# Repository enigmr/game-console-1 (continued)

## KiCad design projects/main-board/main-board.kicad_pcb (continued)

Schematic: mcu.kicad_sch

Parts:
C1, C5, C6, C7, C8, C10, C12, C13, C14, C15, C18, C21, C23, C25, C26, C28, C29, C31, C33, C34, C40, C41, C42, C44, C45, C47: 100nF 10V; C_0402_1005Metric
C2, C9, C17, C20, C22, C30, C32, C36, C37, C38, C39, C43, C46, C48: 1uF 10V; C_0402_1005Metric
C3: 2.2nF 10V; C_0402_1005Metric
C4: 4.7uF 10V; C_0402_1005Metric
C11, C19, C27, C35: 22uF 10V; C_0603_1608Metric
C16, C24: 10uF 10V; C_0603_1608Metric
C109, C110: 9pF 50V; C_0402_1005Metric
C115, C116: 8pF 50V; C_0402_1005Metric
J1, J2: TC2030; Tag-Connect_TC2030-IDC-NL_2x03_P1.27mm_Vertical
L1: 1uH 2.7A 0.054R; IND_0806
L2: 18R; L_0603_1608Metric
L3: 2.2nH 1.4A 0.018R; L_0603_1608Metric
NT1, NT3, NT4, NT5, NT7, NT8, NT9, NT10, NT11, NT12, NT13, NT14: NetTie_2
R1: 2R; R_0402_1005Metric
R2: 200R; R_0402_1005Metric
R3: 10K; R_0402_1005Metric
R4: 50.1K; R_0402_1005Metric
R5, R6, R7, R8: 2.2K; R_0402_1005Metric
R9, R10, R11, R12, R13, R14, R15, R16, R17, R18, R19, R20, R21, R22, R23, R24, R25, R26, R27, R28, R29, R30, R31, R32, R33, R34, R35, R36, R37, R38, R39, R61, R62, R64, R65: 0R; R_0402_1005Metric
U1: STM32N657X0HxQ; STM32N645A0HxQ
Y2: ABM11W-48.0000MHZ-8-K1Z-T3; ABM11W300000MHZ4B1UT3; Manufacturer_Part_Number ABM11W-48.0000MHZ-8-K1Z-T3; Mouser Part Number 815-11W48-8K1ZT
Y3: ABS06-32.768KHZ-9-1-T; ABS06

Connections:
1V8: C1.1, C10.1, C18.1, C26.1, C34.1, C40.1, L2.1, L3.1, NT1.2, NT3.2, NT4.2, NT7.2, NT8.2, NT10.2, NT11.2, NT13.2, NT14.2, U1.G13 (VDD), U1.H12 (VDD), U1.H13 (VDD), U1.J12 (VDD), U1.J13 (VDD), U1.K13 (VDD); also elsewhere on the board
3V3: J1.1, NT5.2, NT9.2, NT12.2, R5.1, R6.1, R7.1, R8.1; also elsewhere on the board
/Audio/I2C.SCL: R5.2, U1.C11 (PE5); also elsewhere on the board
/Audio/I2C.SDA: R7.2, U1.D11 (PE6); also elsewhere on the board
/Audio/I2S.BCK: U1.E17 (PB6); also elsewhere on the board
/Audio/I2S.DACDAT: U1.E16 (PB7); also elsewhere on the board
/Audio/I2S.LRCK: U1.E15 (PB0); also elsewhere on the board
/Audio/I2S.MCLK: U1.F15 (PE2); also elsewhere on the board
/Controllers/BUTTONS.B0: U1.R3 (PF0); also elsewhere on the board
/Controllers/BUTTONS.B1: U1.T1 (PF12); also elsewhere on the board
/Controllers/BUTTONS.B2: U1.P2 (PG4); also elsewhere on the board
/Controllers/BUTTONS.B3: U1.F4 (PH4); also elsewhere on the board
/Controllers/BUTTONS.B4: U1.L2 (PF4); also elsewhere on the board
/Controllers/BUTTONS.B5: U1.B1 (PH3); also elsewhere on the board
/Controllers/BUTTONS.B6: U1.L1 (PG7); also elsewhere on the board
/Controllers/BUTTONS.B7: U1.M1 (PF7); also elsewhere on the board
/Controllers/BUTTONS.B8: U1.B2 (PH6); also elsewhere on the board
/Controllers/BUTTONS.B9: U1.P1 (PF9); also elsewhere on the board
/ESP32/ESP32_GPIO.2: U1.C8 (PC12); also elsewhere on the board
/ESP32/ESP32_GPIO.3: U1.A13 (PD10); also elsewhere on the board
/ESP32/ESP32_GPIO.8: U1.F3 (PC13); also elsewhere on the board
/ESP32/ESP32_GPIO.9: U1.A14 (PD1); also elsewhere on the board
/ESP32/ESP32_UART.RX: U1.F17 (PE1); also elsewhere on the board
/ESP32/ESP32_UART.TX: U1.F16 (PE0); also elsewhere on the board
/Flash/FLASH_OCTOSPI.CS_N: R10.2; also elsewhere on the board
/Flash/FLASH_OCTOSPI.DQS: R9.2; also elsewhere on the board
/Flash/FLASH_OCTOSPI.RESET_N: U1.T16 (PN7); also elsewhere on the board
/Flash/FLASH_OCTOSPI.SCLK: R15.2; also elsewhere on the board
/Flash/FLASH_OCTOSPI.SIO0: R11.2; also elsewhere on the board
/Flash/FLASH_OCTOSPI.SIO1: R12.2; also elsewhere on the board
/Flash/FLASH_OCTOSPI.SIO2: R13.2; also elsewhere on the board
/Flash/FLASH_OCTOSPI.SIO3: R14.2; also elsewhere on the board
/Flash/FLASH_OCTOSPI.SIO4: R16.2; also elsewhere on the board
/Flash/FLASH_OCTOSPI.SIO5: R17.2; also elsewhere on the board
/Flash/FLASH_OCTOSPI.SIO6: R18.2; also elsewhere on the board
/Flash/FLASH_OCTOSPI.SIO7: R19.2; also elsewhere on the board
/Haptics/LEFT_MOTOR_EN: U1.D5 (PQ5); also elsewhere on the board
/Haptics/MOTOR_PWR_EN: U1.A16 (PE9); also elsewhere on the board
/Haptics/RIGHT_MOTOR_EN: U1.G5 (PQ7); also elsewhere on the board
/LCD/BACKLIGHT_PWM: U1.B9 (PC6); also elsewhere on the board
/LCD/LCD.B0: U1.R6 (PG15); also elsewhere on the board
/LCD/LCD.B1: U1.R12 (PA7); also elsewhere on the board
/LCD/LCD.B2: U1.U7 (PA12); also elsewhere on the board
/LCD/LCD.B3: U1.T7 (PA11); also elsewhere on the board
/LCD/LCD.B4: U1.R7 (PA10); also elsewhere on the board
/LCD/LCD.B5: U1.P7 (PA9); also elsewhere on the board
/LCD/LCD.B6: U1.U8 (PA8); also elsewhere on the board
/LCD/LCD.B7: U1.T8 (PA2); also elsewhere on the board
/LCD/LCD.CLK: U1.R8 (PA5); also elsewhere on the board
/LCD/LCD.DE: U1.U9 (PG13); also elsewhere on the board
/LCD/LCD.EN: U1.U14 (PA4); also elsewhere on the board
/LCD/LCD.G0: U1.T9 (PG12); also elsewhere on the board
/LCD/LCD.G1: U1.R9 (PG1); also elsewhere on the board
/LCD/LCD.G2: U1.P9 (PA1); also elsewhere on the board
/LCD/LCD.G3: U1.U10 (PA0); also elsewhere on the board
/LCD/LCD.G4: U1.T10 (PG10); also elsewhere on the board
/LCD/LCD.G5: U1.R10 (PB12); also elsewhere on the board
/LCD/LCD.G6: U1.P10 (PB11); also elsewhere on the board
/LCD/LCD.G7: U1.T14 (PG8); also elsewhere on the board
/LCD/LCD.HSYNC: U1.P8 (PA6); also elsewhere on the board
/LCD/LCD.R0: U1.R13 (PG0); also elsewhere on the board
/LCD/LCD.R1: U1.L4 (PF10); also elsewhere on the board
/LCD/LCD.R2: U1.U12 (PB5(JTDO/TRACESWO)); also elsewhere on the board
/LCD/LCD.R3: U1.T12 (PB4(NJTRST)); also elsewhere on the board
/LCD/LCD.R4: U1.M2 (PF3); also elsewhere on the board
/LCD/LCD.R5: U1.P12 (PA15(JTDI)); also elsewhere on the board
/LCD/LCD.R6: U1.U13 (PG11); also elsewhere on the board
/LCD/LCD.R7: U1.T13 (PG9); also elsewhere on the board
/LCD/LCD.VSYNC: U1.E11; also elsewhere on the board
/MCU/BOOT0: U1.G4 (BOOT0)
/MCU/DEBUG_UART.RX: J2.1, U1.C14 (PD14)
/MCU/DEBUG_UART.TX: J2.3, U1.D15 (PB9)
/MCU/ESP32_EN: U1.B17 (PB14); also elsewhere on the board
/MCU/I2C4.SCL: R6.2, U1.A11 (PE13); also elsewhere on the board
/MCU/I2C4.SDA: R8.2, U1.B11 (PE14); also elsewhere on the board
/MCU/NRST: J1.3, U1.G3 (NRST)
/MCU/PMIC_ALERT: U1.R2 (PF13); also elsewhere on the board
/MCU/PMIC_CHARGE_EN: U1.R1 (PG3); also elsewhere on the board
/MCU/PMIC_INPUT_VALID: U1.N1 (PF15); also elsewhere on the board
/MCU/PMIC_STATUS: U1.N2 (PF14); also elsewhere on the board
/MCU/RAM_HEXASPI.CLK: R23.2; also elsewhere on the board
/MCU/RAM_HEXASPI.CS_N: R20.2; also elsewhere on the board
/MCU/RAM_HEXASPI.D0: R24.2; also elsewhere on the board
/MCU/RAM_HEXASPI.D1: R25.2; also elsewhere on the board
/MCU/RAM_HEXASPI.D2: R26.2; also elsewhere on the board
/MCU/RAM_HEXASPI.D3: R27.2; also elsewhere on the board
/MCU/RAM_HEXASPI.D4: R28.2; also elsewhere on the board
/MCU/RAM_HEXASPI.D5: R29.2; also elsewhere on the board
/MCU/RAM_HEXASPI.D6: R30.2; also elsewhere on the board
/MCU/RAM_HEXASPI.D7: R31.2; also elsewhere on the board
/MCU/RAM_HEXASPI.D8: R32.2; also elsewhere on the board
/MCU/RAM_HEXASPI.D9: R33.2; also elsewhere on the board
/MCU/RAM_HEXASPI.D10: R34.2; also elsewhere on the board
/MCU/RAM_HEXASPI.D11: R35.2; also elsewhere on the board
/MCU/RAM_HEXASPI.D12: R36.2; also elsewhere on the board
/MCU/RAM_HEXASPI.D13: R37.2; also elsewhere on the board
/MCU/RAM_HEXASPI.D14: R38.2; also elsewhere on the board
/MCU/RAM_HEXASPI.D15: R39.2; also elsewhere on the board
/MCU/RAM_HEXASPI.DQS0: R21.2; also elsewhere on the board
/MCU/RAM_HEXASPI.DQS1: R22.2; also elsewhere on the board
/MCU/SD.CLK: U1.D9 (PC2); also elsewhere on the board
/MCU/SD.CMD: U1.E10 (PC3); also elsewhere on the board
/MCU/SD.D0: U1.A10 (PC4); also elsewhere on the board
/MCU/SD.D1: U1.B10 (PC5); also elsewhere on the board
/MCU/SD.D2: U1.C10 (PC0); also elsewhere on the board
/MCU/SD.D3: U1.D10 (PE4); also elsewhere on the board
/MCU/SD.DETECT: U1.P14 (PN12)
/MCU/SWCLK: J1.4, U1.T6 (PA14(JTCK/SWCLK))
/MCU/SWDIO: J1.2, U1.U6 (PA13(JTMS/SWDIO))
/MCU/USB.DN: U1.A5 (OTG1_HSDM); also elsewhere on the board
/MCU/USB.DP: U1.B5 (OTG1_HSDP); also elsewhere on the board
/MCU/USB_CC1: U1.A6 (UCPD1_CC1)
/MCU/USB_CC2: U1.B6 (UCPD1_CC2)
GND: C1.2, C2.2, C3.2, C4.2, C5.2, C6.2, C7.2, C8.2, C9.2, C10.2, C11.2, C12.2, C13.2, C14.2, C15.2, C16.2, C17.2, C18.2, C19.2, C20.2, C21.2, C22.2, C23.2, C24.2, C25.2, C26.2, C27.2, C28.2, C29.2, C30.2, C31.2, C32.2, C33.2, C34.2, C35.2, C36.2, C37.2, C38.2, C39.2, C40.2, C41.2, C42.2, C43.2, C44.2, C45.2, C46.2, C47.2, C48.2, C109.2, C110.2, C115.2, C116.2, J1.5, J2.5, R2.2, R4.2, U1.A17 (VSS), U1.F2 (VSSAPMU), U1.F7 (VSS), U1.F10 (VSS), U1.F11 (VSS), U1.F12 (VSS), U1.G6 (VSSAON), U1.G12 (VSS), U1.H1 (VSSSMPS), U1.H2 (VSSSMPS), U1.H3 (VSSSMPS), U1.H4 (VSSSMPS), U1.H5 (VSSSMPS), U1.H6 (VSSSMPS), U1.K12 (VSS), U1.M6 (VSSA), U1.M8 (VSS), U1.M10 (VSS), U1.M12 (VSS), U1.M13 (VSS), U1.N5 (VSS), U1.N7 (VSS), U1.N9 (VSS), U1.N11 (VSS), U1.T2 (VREF-), U1.U1 (VSS), U1.U17 (VSS), Y2.2 (GND), Y2.4 (GND); also elsewhere on the board
unnamed: C3.1, R1.2
unnamed: C109.1, R65.1, Y3.1
unnamed: C110.1, R64.1, Y3.2
unnamed: C115.1, R61.2, Y2.1
unnamed: C116.1, R62.2, Y2.3
unnamed: L1.1, R1.1, U1.J1 (VLXSMPS), U1.J2 (VLXSMPS), U1.J3 (VLXSMPS), U1.J4 (VLXSMPS), U1.J5 (VLXSMPS), U1.J6 (VLXSMPS)
unnamed: R65.2, U1.D1 (PC14-OSC32_IN(OSC32_IN))
unnamed: R64.2, U1.C1 (PC15-OSC32_OUT(OSC32_OUT))
unnamed: R61.1, U1.A7 (PH0-OSC_IN(PH0))
unnamed: R62.1, U1.B7 (PH1-OSC_OUT(PH1))
unnamed: R9.1, U1.P17 (PN0)
unnamed: R10.1, U1.R17 (PN1)
unnamed: R11.1, U1.T17 (PN2)
unnamed: R12.1, U1.R15 (PN3)
unnamed: R13.1, U1.N17 (PN4)
unnamed: R14.1, U1.R16 (PN5)
unnamed: R15.1, U1.P15 (PN6)
unnamed: R16.1, U1.P16 (PN8)
unnamed: R17.1, U1.T15 (PN9)
unnamed: R18.1, U1.U15 (PN10)
unnamed: R19.1, U1.U16 (PN11)
unnamed: R20.1, U1.M17 (PO0)
unnamed: R21.1, U1.K17 (PO2)
unnamed: R22.1, U1.M16 (PO3)
unnamed: R23.1, U1.N16 (PO4)
unnamed: R2.1, U1.C6 (OTG1_TXRTUNE)
unnamed: C12.1, R3.2, R4.1, U1.E1 (VBAT)
unnamed: R24.1, U1.G17 (PP0)
unnamed: R25.1, U1.H16 (PP1)
unnamed: R26.1, U1.J17 (PP2)
unnamed: R27.1, U1.J16 (PP3)
unnamed: R28.1, U1.H15 (PP4)
unnamed: R29.1, U1.J14 (PP5)
unnamed: R30.1, U1.G16 (PP6)
unnamed: R31.1, U1.G15 (PP7)
unnamed: R32.1, U1.L16 (PP8)
unnamed: R33.1, U1.N14 (PP9)
unnamed: R34.1, U1.N15 (PP10)
unnamed: R35.1, U1.L15 (PP11)
unnamed: R36.1, U1.J15 (PP12)
unnamed: R37.1, U1.K14 (PP13)
unnamed: R38.1, U1.L17 (PP14)
unnamed: R39.1, U1.H17 (PP15)
V08CAP: C4.1, U1.F1 (V08CAP)
VBAT: R3.1; also elsewhere on the board
VDDA18ADC: C29.1, NT11.1, U1.N6 (VDDA18ADC)
VDDA18AON: C5.1, NT1.1, U1.A1 (PDR_ON), U1.F6 (VDDA18AON)
VDDA18CSI: C6.1, NT3.1, U1.R5 (VDDA18CSI)
VDDA18PLL: C42.1, NT14.1, U1.M5 (VDDA18PLL)
VDDA18PMU: C13.1, L2.2, U1.G1 (VDDA18PMU)
VDDA18USB: C21.1, NT8.1, U1.C5 (VDDA18USB)
VDDA33USB: C38.1, NT12.1, U1.A4 (VDD33USB)
VDDCORE: C2.1, C9.1, C11.1, C17.1, C19.1, C22.1, C27.1, C30.1, C35.1, C37.1, C43.1, C46.1, C48.1, L1.2, U1.G2 (VFBSMPS), U1.L6 (VDDCORE), U1.L12 (VDDCORE), U1.M7 (VDDCORE), U1.M9 (VDDCORE), U1.M11 (VDDCORE), U1.N8 (VDDCORE), U1.N10 (VDDCORE), U1.N12 (VDDCORE), U1.P11 (VDDCORE)
VDDCSI: C20.1, NT7.1, U1.R4 (VDDCSI)
VDDIO2: C7.1, C14.1, C23.1, C31.1, NT4.1, U1.L13 (VDDIO2), U1.L14 (VDDIO2), U1.M14 (VDDIO2), U1.M15 (VDDIO2)
VDDIO3: C41.1, C45.1, NT13.1, U1.N13 (VDDIO3), U1.P13 (VDDIO3)
VDDIO4: C8.1, C15.1, NT5.1, U1.E8 (VDDIO4), U1.F8 (VDDIO4)
VDDIO5: C25.1, C33.1, NT9.1, U1.E9 (VDDIO5), U1.F9 (VDDIO5)
VDDSMPS: C16.1, C24.1, C32.1, C39.1, C44.1, C47.1, L3.2, U1.K1 (VDDSMPS), U1.K2 (VDDSMPS), U1.K3 (VDDSMPS), U1.K4 (VDDSMPS), U1.K5 (VDDSMPS), U1.K6 (VDDSMPS)
VREF: C28.1, C36.1, NT10.1, U1.U2 (VREF+)

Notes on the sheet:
USART10_RX
SAI1_MCLK_A
USART3_RX
USART3_TX
USART10_TX
TIM8_CH3
TIM8_CH2
SAI1_SD_A
SAI1_SCK_A
TIM9_CH1
SAI1_FS_A

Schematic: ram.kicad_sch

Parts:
C49, C50: 100nF 10V; C_0402_1005Metric
C51, C52: 4.7uF 10V; C_0402_1005Metric
R40: 10K; R_0402_1005Metric
U2: APS256XXN-OBR-BG

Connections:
1V8: C49.1, C50.1, C51.1, C52.1, R40.1, U2.D1 (VDD), U2.E4 (VDD); also elsewhere on the board
/MCU/RAM_HEXASPI.CLK: U2.B2 (CLK); also elsewhere on the board
/MCU/RAM_HEXASPI.CS_N: R40.2, U2.A3 (CE#); also elsewhere on the board
/MCU/RAM_HEXASPI.D0: U2.D3 (ADQ0); also elsewhere on the board
/MCU/RAM_HEXASPI.D1: U2.D2 (ADQ1); also elsewhere on the board
/MCU/RAM_HEXASPI.D2: U2.C4 (ADQ2); also elsewhere on the board
/MCU/RAM_HEXASPI.D3: U2.D4 (ADQ3); also elsewhere on the board
/MCU/RAM_HEXASPI.D4: U2.D5 (ADQ4); also elsewhere on the board
/MCU/RAM_HEXASPI.D5: U2.E3 (ADQ5); also elsewhere on the board
/MCU/RAM_HEXASPI.D6: U2.E2 (ADQ6); also elsewhere on the board
/MCU/RAM_HEXASPI.D7: U2.E1 (ADQ7); also elsewhere on the board
/MCU/RAM_HEXASPI.D8: U2.C2 (DQ8); also elsewhere on the board
/MCU/RAM_HEXASPI.D9: U2.B1 (DQ9); also elsewhere on the board
/MCU/RAM_HEXASPI.D10: U2.A2 (DQ10); also elsewhere on the board
/MCU/RAM_HEXASPI.D11: U2.A4 (DQ11); also elsewhere on the board
/MCU/RAM_HEXASPI.D12: U2.A5 (DQ12); also elsewhere on the board
/MCU/RAM_HEXASPI.D13: U2.B4 (DQ13); also elsewhere on the board
/MCU/RAM_HEXASPI.D14: U2.B5 (DQ14); also elsewhere on the board
/MCU/RAM_HEXASPI.D15: U2.C5 (DQ15); also elsewhere on the board
/MCU/RAM_HEXASPI.DQS0: U2.C3 (DQS/DM0); also elsewhere on the board
/MCU/RAM_HEXASPI.DQS1: U2.B3 (DQS/DM1); also elsewhere on the board
GND: C49.2, C50.2, C51.2, C52.2, U2.C1 (VSS), U2.E5 (VSS); also elsewhere on the board

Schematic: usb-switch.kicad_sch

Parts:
C74: 100nF 10V; C_0402_1005Metric
U8: TS3USB221ARSER

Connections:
3V3: C74.1, U8.10 (VCC); also elsewhere on the board
/MCU/USB.DN: U8.2 (1D-); also elsewhere on the board
/MCU/USB.DP: U8.1 (1D+); also elsewhere on the board
/Power/DATAMUX: U8.9 (S); also elsewhere on the board
/Power/USB.DN: U8.4 (2D-); also elsewhere on the board
/Power/USB.DP: U8.3 (2D+); also elsewhere on the board
/USB Switch/USB_UP.DN: U8.7 (D-); also elsewhere on the board
/USB Switch/USB_UP.DP: U8.8 (D+); also elsewhere on the board
GND: C74.2, U8.5 (GND), U8.6 (OE_N); also elsewhere on the board

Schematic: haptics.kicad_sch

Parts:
C100, C102: 10uF 10V; C_0603_1608Metric
C101, C103: 100nF 10V; C_0402_1005Metric
NT2: NetTie_2
Q1, Q2: ZXTN4240F-7; SOT23_ZXTN_DIO
R57: 10K; R_0402_1005Metric
R58, R59: 1K; R_0402_1005Metric
U12: TLV74330PDBVR

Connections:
/Controllers/LEFT_MOTOR.N: Q1.1 (C); also elsewhere on the board
/Controllers/LEFT_MOTOR.P: C102.1, C103.1, NT2.1, U12.5 (OUT); also elsewhere on the board
/Controllers/RIGHT_MOTOR.N: Q2.1 (C); also elsewhere on the board
/Haptics/LEFT_MOTOR_EN: R58.1; also elsewhere on the board
/Haptics/MOTOR_PWR_EN: R57.1, U12.3 (EN); also elsewhere on the board
/Haptics/RIGHT_MOTOR_EN: R59.1; also elsewhere on the board
GND: C100.2, C101.2, C102.2, C103.2, Q1.3 (E), Q2.3 (E), R57.2, U12.2 (GND), U12.4 (NC); also elsewhere on the board
unnamed: Q1.2 (B), R58.2
unnamed: Q2.2 (B), R59.2
VSYS: C100.1, C101.1, U12.1 (IN); also elsewhere on the board

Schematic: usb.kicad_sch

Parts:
J7: USB4105-GF-A

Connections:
/USB Switch/USB_UP.DN: J7.A7 (Dn1), J7.B7 (Dn2); also elsewhere on the board
/USB Switch/USB_UP.DP: J7.A6 (Dp1), J7.B6 (Dp2); also elsewhere on the board
/USB/USB_CC1: J7.A5 (CC1); also elsewhere on the board
/USB/USB_CC2: J7.B5 (CC2); also elsewhere on the board
GND: J7.A1 (GND), J7.B1 (GND), J7.SH1 (GND), J7.SH2 (GND), J7.SH3 (GND), J7.SH4 (GND); also elsewhere on the board
VBUS: J7.A4 (VBUS), J7.B4 (VBUS); also elsewhere on the board

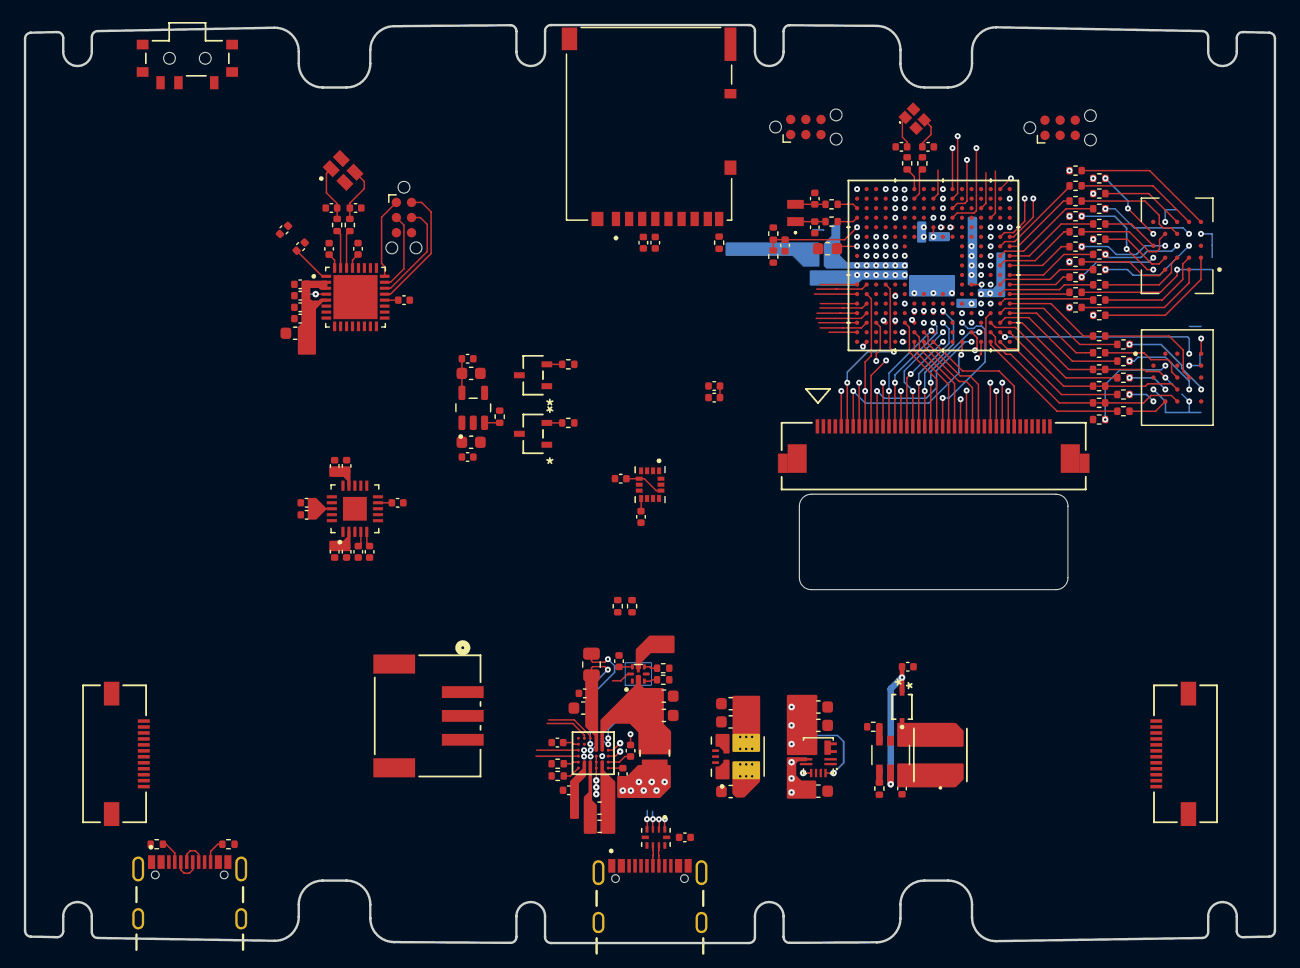
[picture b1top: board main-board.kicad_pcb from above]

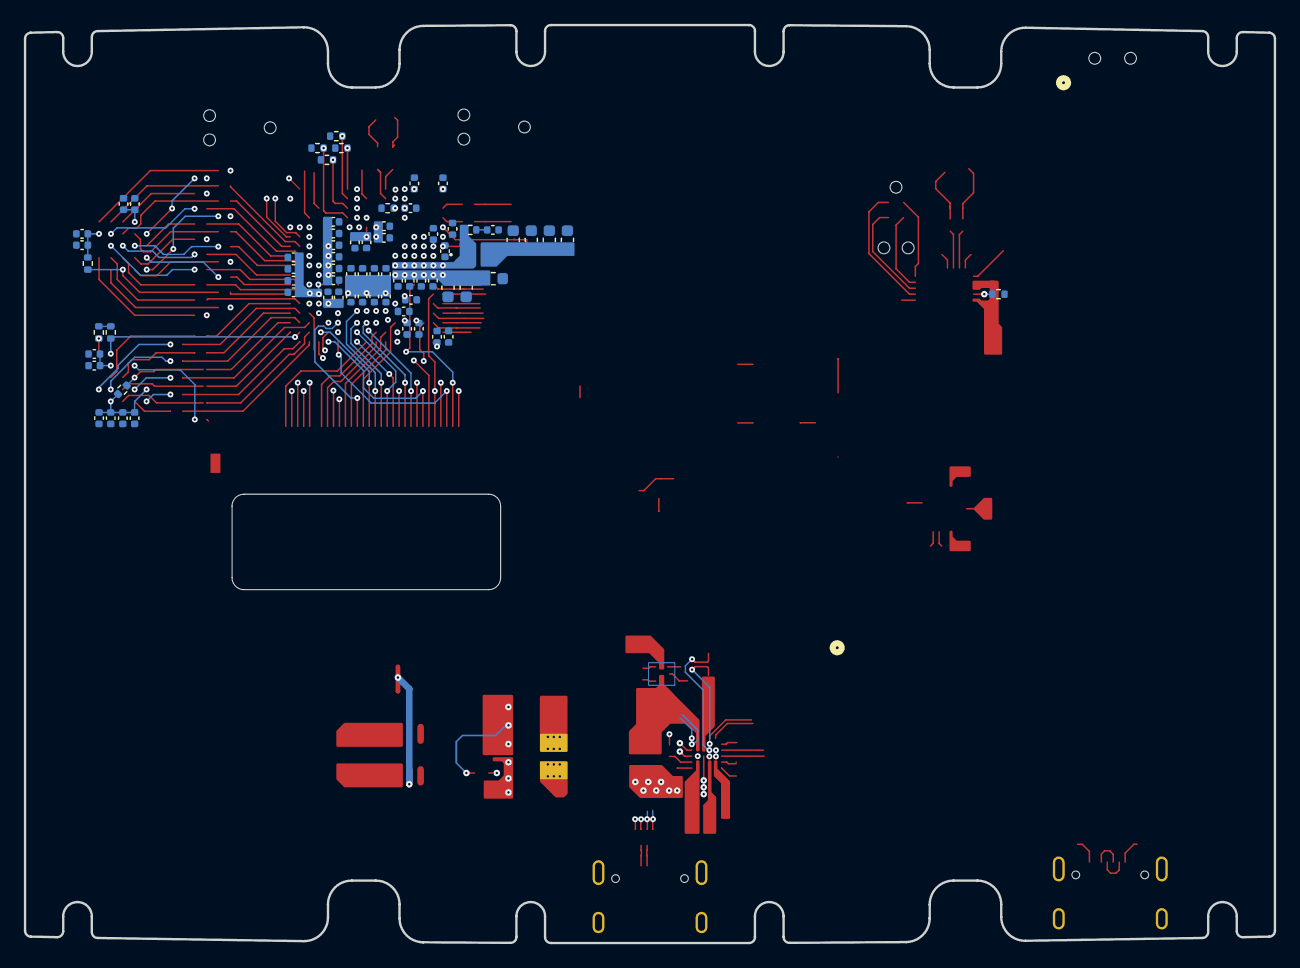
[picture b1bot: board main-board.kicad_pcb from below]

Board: 6 copper layers, 104.8 x 77.0 mm, 213 parts (70 on the bottom side), 219 nets.

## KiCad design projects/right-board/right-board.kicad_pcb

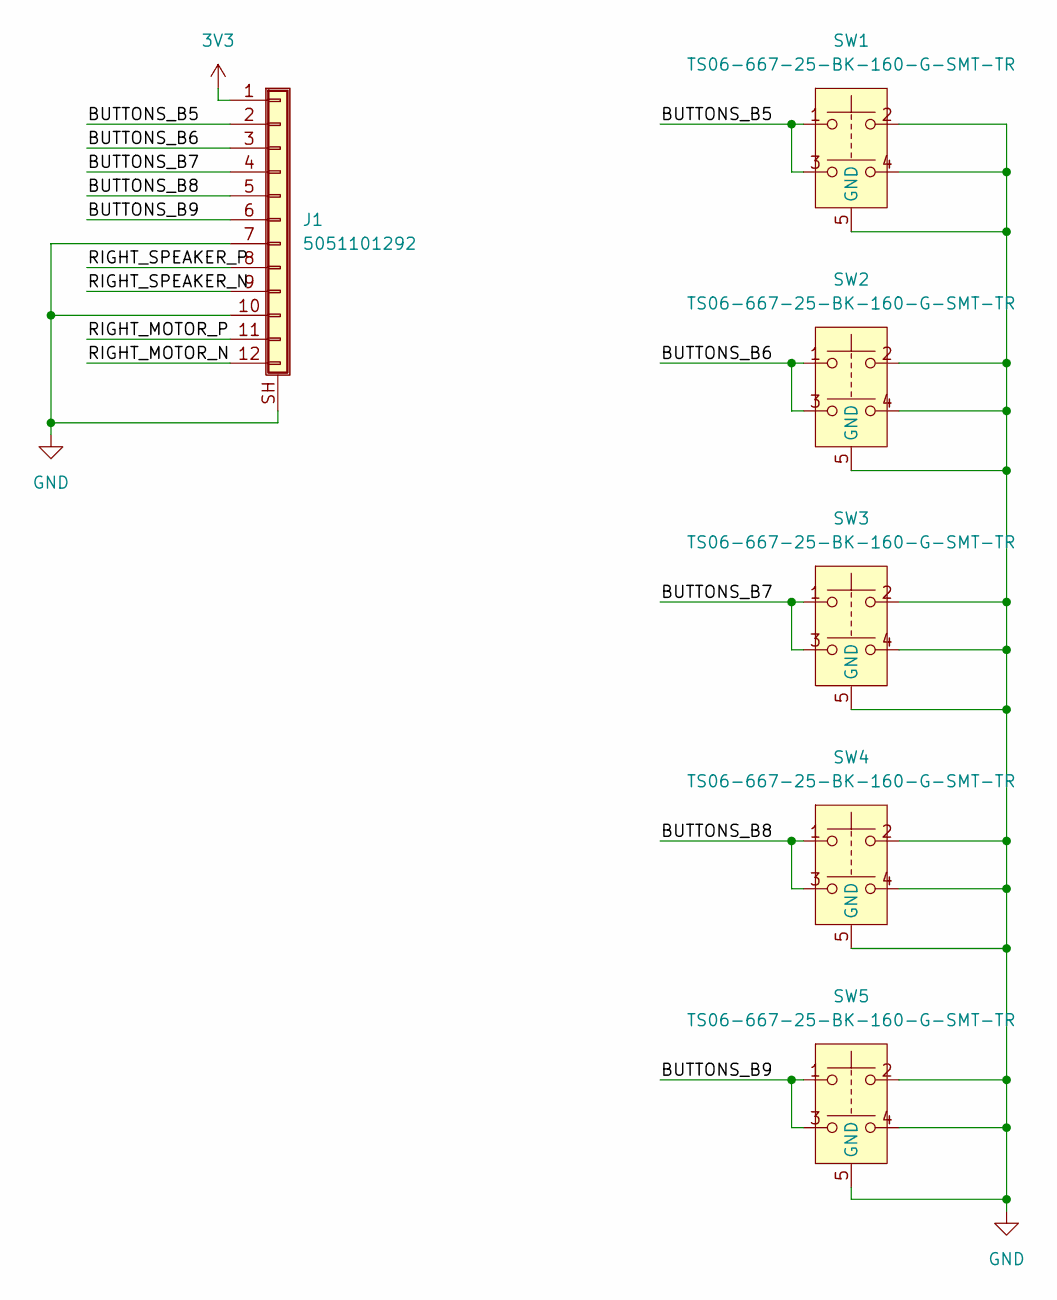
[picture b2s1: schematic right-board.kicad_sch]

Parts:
J1: 5051101292
SW1, SW2, SW3, SW4, SW5: TS06-667-25-BK-160-G-SMT-TR

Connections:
3V3: J1.1
/BUTTONS_B5: J1.2, SW1.1, SW1.3
/BUTTONS_B6: J1.3, SW2.1, SW2.3
/BUTTONS_B7: J1.4, SW3.1, SW3.3
/BUTTONS_B8: J1.5, SW4.1, SW4.3
/BUTTONS_B9: J1.6, SW5.1, SW5.3
/RIGHT_MOTOR_N: J1.12
/RIGHT_MOTOR_P: J1.11
/RIGHT_SPEAKER_N: J1.9
/RIGHT_SPEAKER_P: J1.8
GND: J1.7, J1.10, J1.SH (Shield), SW1.2, SW1.4, SW1.5 (GND), SW2.2, SW2.4, SW2.5 (GND), SW3.2, SW3.4, SW3.5 (GND), SW4.2, SW4.4, SW4.5 (GND), SW5.2, SW5.4, SW5.5 (GND)

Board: 2 copper layers, 6 parts (5 on the bottom side), 6 nets, no tracks yet.

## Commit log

2025-07-26 Add footprints and 3D models
2025-07-26 Updated schematics with new symbols
2025-07-26 Re-annotate schematics.
2025-07-26 Replace 0.1in header with TC2030
2025-07-26 Update schematic SVGs
2025-07-26 Add capacitor part library.
2025-07-26 Normalise capacitors
    - Add capacitor parts to library.
    - Replace all placeholder capacitors
    with the actual part numbers.
2025-07-26 Add resistor library
2025-07-26 Replace placeholder resistors
2025-07-27 Add footprints
    - Inductors
    - Switches
    - Buttons
2025-07-27 Add board design rules
2025-07-27 Fix footprint DRC errors.
2025-07-27 Rough PCB component grouping and layout
2025-07-27 Update renders.
2025-07-27 Update images. Add render.
2025-07-27 Fix wrong image paths in readme.
2025-07-27 Update render.
2025-07-29 Update render
2025-07-30 Update PCB profile and render
2025-08-03 Main board PCB layout and routing
    - Add 48MHz crystal for STM32
    - Add 32kHz crystal for STM32
    - Started laying out and routing board
2025-08-04 PCB layout and renders
2025-08-19 Routed LCD signals
2025-08-20 More routing of main board
2025-08-24 WIP splitting main board into 3
2025-08-24 Reorganise repo to support multiple PCBs
2025-08-24 Add left board
2025-08-24 Add right board
2025-08-24 Fix wrong net name on left audio
2025-08-24 Remove backup files
2025-08-24 Position board-to-board connectors
2025-08-24 Update pictures
2025-08-24 Update renders
